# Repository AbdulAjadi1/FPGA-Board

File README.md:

# Custom Zynq FPGA Development Board

A custom-designed 8-layer FPGA development board based on the Xilinx Zynq-7000 SoC, featuring DDR3 memory, high-speed interfaces, and multi-rail power architecture. Designed from schematic through PCB layout and hardware bring-up.

---

<h2>🎥 FPGA Board Overview Demo</h2>

<h2>🔬 Full DDR3 Bring-Up Walkthrough (Vivado → Vitis)</h2>

<h2>💾 QSPI Flash Bring-Up Demo</h2>

<h2>🔌 UART Using EMIO and DDR3 test</h2>

---

**Custom Zynq-7000 FPGA Development Board**

**Overview**

This project is a custom FPGA development board inspired by the Digilent Arty Z7 platform, designed around the Xilinx Zynq-7000 SoC. The board serves as a general-purpose hardware development and learning platform, with an emphasis on FPGA and ARM (PS/PL) co-design, sound, power and signal-integrity practices, manufacturable industry-style PCB layout, and realistic interfaces commonly used in embedded and FPGA systems. The design is intended for advanced manufacturing and assembly at JLCPCB.

The project targets entry-level to junior FPGA and hardware engineering roles and focuses on demonstrating practical, board-level engineering decisions rather than a minimal breakout-style design.

**Project Status:**

## 🧪 Bring-Up & Validation

- ✅ DDR3 bring-up completed with successful memory test execution  
- ✅ QSPI flash configuration verified  
- ✅ FTDI USB-to-JTAG interface operational for programming and debug  
- ✅ Multi-rail power system validated 
- ✅ AXI GPIO controlling user LEDs and RGB LEDs confirmed  
- ✅ PS clocking and PLL configuration stable

**KEY FEATURES:**
- Xilinx Zynq-7000 SoC (Z7-20 / XC7Z020 class)
- DDR3 SDRAM (PS memory)
- HDMI interface (video output)
- Ethernet PHY (10/100/1000 Mbps)
- USB Host
- USB-JTAG interface
- SPDIF / TOSLINK interface
- QSPI Flash (boot storage)
- microSD card support
- PMOD / GPIO headers
- 40-pin Raspberry Pi interface
- On-board oscillators for PS and PL
- User LEDs, buttons, and switches
- Multi-rail power tree with switching regulators and LDOs

**DESIGN GOALS:**
- Follow Xilinx Zynq hardware design guidelines
- Implement correct decoupling, grounding, and plane usage
- Use controlled-impedance routing for high-speed interfaces
- Be compatible with low-cost PCB manufacturing and assembly
- Serve as a portfolio-quality hardware project

**HARDWARE ARCHITECTURE:**
- Zynq SoC
- ARM Cortex-A9 Processing System (PS)
- Programmable Logic (PL) fabric
- PS-to-PL interconnect exposed for custom designs
- Boot modes supported via QSPI / SD Memory
- DDR3 SDRAM connected to the PS:
- Length-matched address, control, and data groups
- Proper VREF routing and decoupling

**POWER TREE:**

**Input Sources:**

- 7-15V Barrel jack
- Raspberry pi 5V
- USB 5V

**Generated rails:**

- 1.0 V (FPGA core)

- 1.5 V (DDR3)

- 1.8 V (aux, IO)

- 3.3 V (IO and peripherals)

**PCB DESIGN DETAILS:**

- 8-layer PCB stackup

- Dedicated solid ground planeS

- Power planes for core rails

- Signal layers for controlled routing

- Thermal via stitching under FPGA ground regions

**Controlled impedance routing for:**

- DDR3 100Ω diff ±10%, 50Ω single ±10%

- HDMI 100Ω diff ±10%

- Ethernet  100Ω diff ±10%, 50Ω single ±10%

- USB 100Ω diff ±10%, 50Ω single ±10%

- SD  50Ω single ±10%

**INTENDED USE CASES:**

- FPGA and SoC learning platform

- PS/PL co-design experimentation

- HDL development and verification

- Embedded Linux bring-up (future work)

**TOOLS USED:**

- KiCad – schematic capture and PCB layout

- Xilinx Vivado – FPGA design and synthesis

- Vendor datasheets and Xilinx reference designs

- JLCPCB DFM/DFT tools

- JLCPCB Impedance calculator

**Author**

Designed and documented by Abdul Ajadi

Electronics / FPGA Hardware Engineer

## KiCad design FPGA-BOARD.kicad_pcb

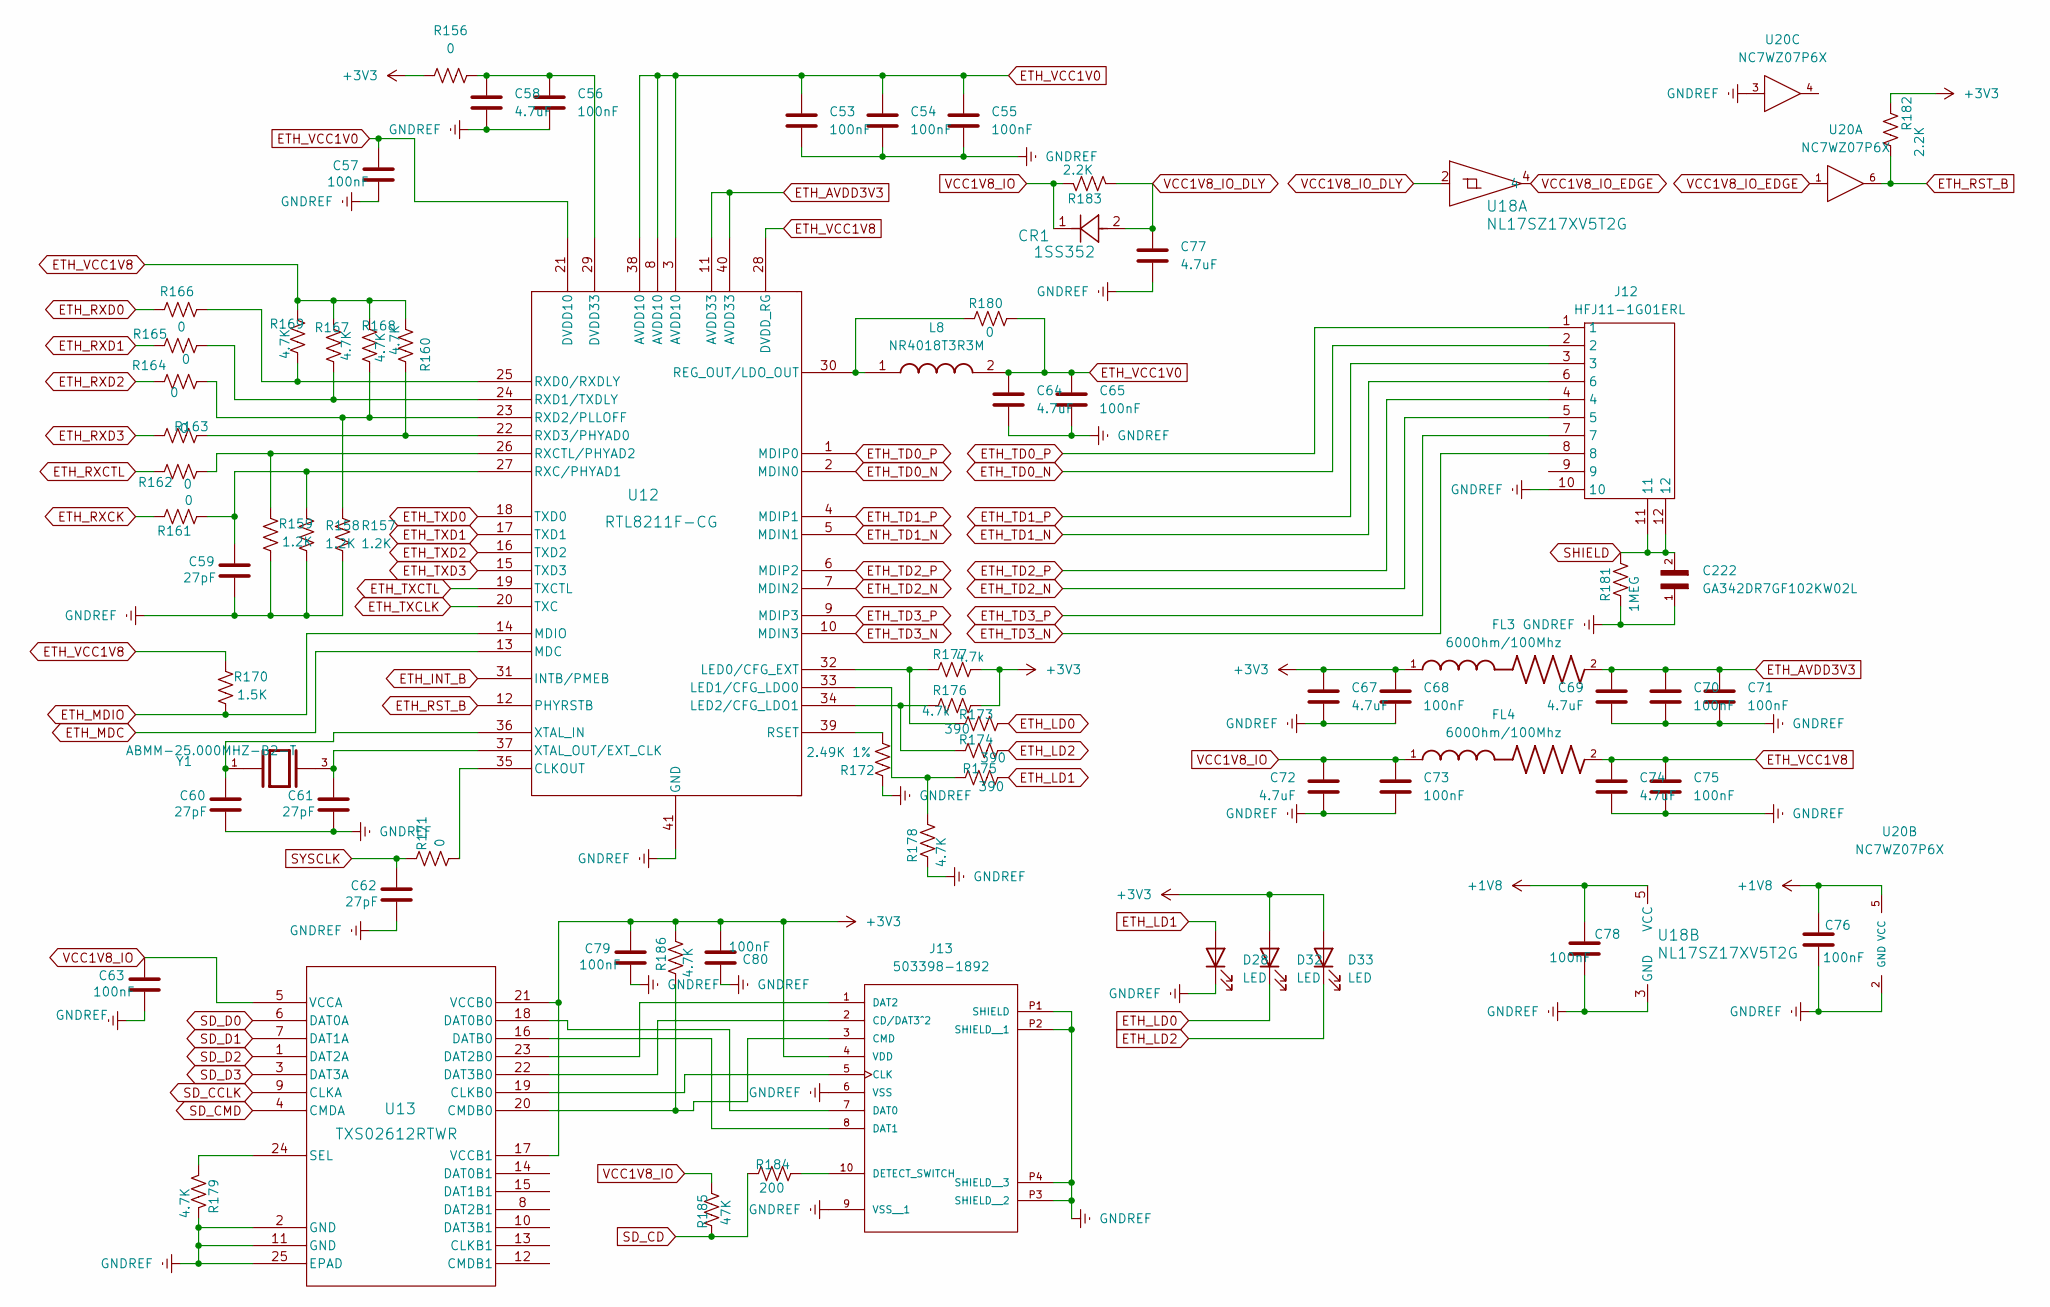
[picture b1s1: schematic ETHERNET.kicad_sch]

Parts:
C53, C54, C55, C56, C57, C63, C65, C68, C70, C71, C73, C75, C76, C78, C79, C80: 100nF; C_0201_0603Metric; LCSC PN c307380
C58, C64, C67, C69, C72, C74, C77: 4.7uF; C_0402; LCSC PN C2858031
C59, C60, C61, C62: 27pF; C_0201_0603Metric; LCSC PN C161381
C222: GA342DR7GF102KW02L; CAPC4520X220N; LCSC PN C237595
CR1: 1SS352; USC_TOS; LCSC PN C15885
D28, D32, D33: LED; LED_0402_1005Metric; LCSC PN C130723
FL3, FL4: 600Ohm/100Mhz; BEADC1608X95N; LCSC PN C19330
J12: HFJ11-1G01ERL; HALO_FASTJACK; Mouser Part Number 493-HFJ11-1G01ERL
J13: 503398-1892; MOLEX_503398-1892; PARTREV 0; LCSC PN C428492
L8: NR4018T3R3M; Mouser Part Number 963-NR4018T3R3M
R156, R171, R180: 0; R_0402; LCSC PN C106231
R157, R158, R159: 1.2K; R_0201_0603Metric; LCSC PN C327393
R160, R167, R168, R169, R178, R179, R186: 4.7K; R_0201_0603Metric; LCSC PN C138135
R161, R162, R163, R164, R165, R166: 0; R_0201_0603Metric; LCSC PN c106228
R170: 1.5K; R_0402; LCSC PN C114759
R172: 2.49K 1%; R_0402; LCSC PN C145071
R173, R174, R175: 390; R_0402; LCSC PN C137997
R176, R177: 4.7k; R_0402; LCSC PN C105871
R181: 1MEG; R_0402; LCSC PN C138033
R182, R183: 2.2K; R_0402; LCSC PN c114762
R184: 200; R_0402; LCSC PN C114764
R185: 47K; R_0402; LCSC PN C93943
U12: RTL8211F-CG; RTL8211F-CG_RTK; LCSC PN C187932
U13: TXS02612RTWR; RTW24_2P45X2P45; LCSC PN C140276
U18: NL17SZ17XV5T2G; SOT553-5_ONS; LCSC PN C152502
U20: NC7WZ07P6X; MPN NC7WZ07P6X; LCSC PN C95342
Y1: ABMM-25.000MHZ-B2-T; XTAL_ABMM-25.000MHZ-B2-T; PARTREV 02.26.12; LCSC PN C596927

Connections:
+1V8: C76.1, C78.1, U18.5 (VCC), U20.5 (VCC); also elsewhere on the board
+3V3: C67.1, C68.1, C79.1, C80.1, D32.2 (A), D33.2 (A), FL3.1, J13.4 (VDD), R156.2, R176.2, R177.2, R182.2, R186.2, U13.17 (VCCB1), U13.21 (VCCB0); also elsewhere on the board
ETH_AVDD3V3: C69.1, C70.1, C71.1, FL3.2, U12.11 (AVDD33), U12.40 (AVDD33)
ETH_INT_B: U12.31 (INTB/PMEB); also elsewhere on the board
ETH_LD0: D32.1 (K), R173.2
ETH_LD1: D28.2 (A), R175.2
ETH_LD2: D33.1 (K), R174.2
ETH_MDC: U12.13 (MDC); also elsewhere on the board
ETH_MDIO: R170.2, U12.14 (MDIO); also elsewhere on the board
ETH_RST_B: R182.1, U12.12 (PHYRSTB), U20.6; also elsewhere on the board
ETH_RXCK: R161.2; also elsewhere on the board
ETH_RXCTL: R162.2; also elsewhere on the board
ETH_RXD0: R166.2; also elsewhere on the board
ETH_RXD1: R165.2; also elsewhere on the board
ETH_RXD2: R164.2; also elsewhere on the board
ETH_RXD3: R163.2; also elsewhere on the board
ETH_TD0_N: J12.2, U12.2 (MDIN0)
ETH_TD0_P: J12.1, U12.1 (MDIP0)
ETH_TD1_N: J12.6, U12.5 (MDIN1)
ETH_TD1_P: J12.3, U12.4 (MDIP1)
ETH_TD2_N: J12.5, U12.7 (MDIN2)
ETH_TD2_P: J12.4, U12.6 (MDIP2)
ETH_TD3_N: J12.8, U12.10 (MDIN3)
ETH_TD3_P: J12.7, U12.9 (MDIP3)
ETH_TXCLK: U12.20 (TXC); also elsewhere on the board
ETH_TXCTL: U12.19 (TXCTL); also elsewhere on the board
ETH_TXD0: U12.18 (TXD0); also elsewhere on the board
ETH_TXD1: U12.17 (TXD1); also elsewhere on the board
ETH_TXD2: U12.16 (TXD2); also elsewhere on the board
ETH_TXD3: U12.15 (TXD3); also elsewhere on the board
ETH_VCC1V0: C53.1, C54.1, C55.1, C57.1, C64.1, C65.1, L8.2, R180.2, U12.3 (AVDD10), U12.8 (AVDD10), U12.21 (DVDD10), U12.38 (AVDD10)
ETH_VCC1V8: C74.1, C75.1, FL4.2, R160.1, R167.1, R168.1, R169.1, R170.1, U12.28 (DVDD_RG)
GNDREF: C53.2, C54.2, C55.2, C56.2, C57.2, C58.2, C59.2, C60.2, C61.2, C62.2, C63.2, C64.2, C65.2, C67.2, C68.2, C69.2, C70.2, C71.2, C72.2, C73.2, C74.2, C75.2, C76.2, C77.2, C78.2, C79.2, C80.2, C222.1, D28.1 (K), J12.10, J13.6 (VSS), J13.9 (VSS__1), J13.P1 (SHIELD), J13.P2 (SHIELD__1), J13.P3 (SHIELD__2), J13.P4 (SHIELD__3), R157.2, R158.2, R159.2, R172.1, R178.1, R179.1, R181.1, U12.41 (GND), U13.2 (GND), U13.11 (GND), U13.25 (EPAD), U13.V, U18.3 (GND), U20.2 (GND), U20.3; also elsewhere on the board
unnamed: J13.2 (CD/DAT3^2), U13.22 (DAT3B0)
unnamed: J13.5 (CLK), U13.19 (CLKB0)
unnamed: J13.3 (CMD), R186.1, U13.20 (CMDB0)
unnamed: J13.7 (DAT0), U13.18 (DAT0B0)
unnamed: J13.8 (DAT1), U13.16 (DATB0)
unnamed: J13.1 (DAT2), U13.23 (DAT2B0)
unnamed: J13.10 (DETECT_SWITCH), R184.2
unnamed: R171.2, U12.35 (CLKOUT)
unnamed: C56.1, C58.1, R156.1, U12.29 (DVDD33)
unnamed: R173.1, R177.1, U12.32 (LED0/CFG_EXT)
unnamed: R175.1, R178.2, U12.33 (LED1/CFG_LDO0)
unnamed: R174.1, R176.1, U12.34 (LED2/CFG_LDO1)
unnamed: L8.1, R180.1, U12.30 (REG_OUT/LDO_OUT)
unnamed: R172.2, U12.39 (RSET)
unnamed: R159.1, R162.1, U12.26 (RXCTL/PHYAD2)
unnamed: C59.1, R158.1, R161.1, U12.27 (RXC/PHYAD1)
unnamed: R166.1, R169.2, U12.25 (RXD0/RXDLY)
unnamed: R165.1, R167.2, U12.24 (RXD1/TXDLY)
unnamed: R157.1, R164.1, R168.2, U12.23 (RXD2/PLLOFF)
unnamed: R160.2, R163.1, U12.22 (RXD3/PHYAD0)
unnamed: C60.1, U12.36 (XTAL_IN), Y1.1
unnamed: C61.1, U12.37 (XTAL_OUT/EXT_CLK), Y1.3
unnamed: R179.2, U13.24 (SEL)
SD_CCLK: U13.9 (CLKA); also elsewhere on the board
SD_CD: R184.1, R185.1; also elsewhere on the board
SD_CMD: U13.4 (CMDA); also elsewhere on the board
SD_D0: U13.6 (DAT0A); also elsewhere on the board
SD_D1: U13.7 (DAT1A); also elsewhere on the board
SD_D2: U13.1 (DAT2A); also elsewhere on the board
SD_D3: U13.3 (DAT3A); also elsewhere on the board
SHIELD: C222.2, J12.11, J12.12, R181.2
SYSCLK: C62.1, R171.1; also elsewhere on the board
VCC1V8_IO: C63.1, C72.1, C73.1, CR1.1, FL4.1, R183.1, R185.2, U13.5 (VCCA); also elsewhere on the board
VCC1V8_IO_DLY: C77.1, CR1.2, R183.2, U18.2
VCC1V8_IO_EDGE: U18.4, U20.1

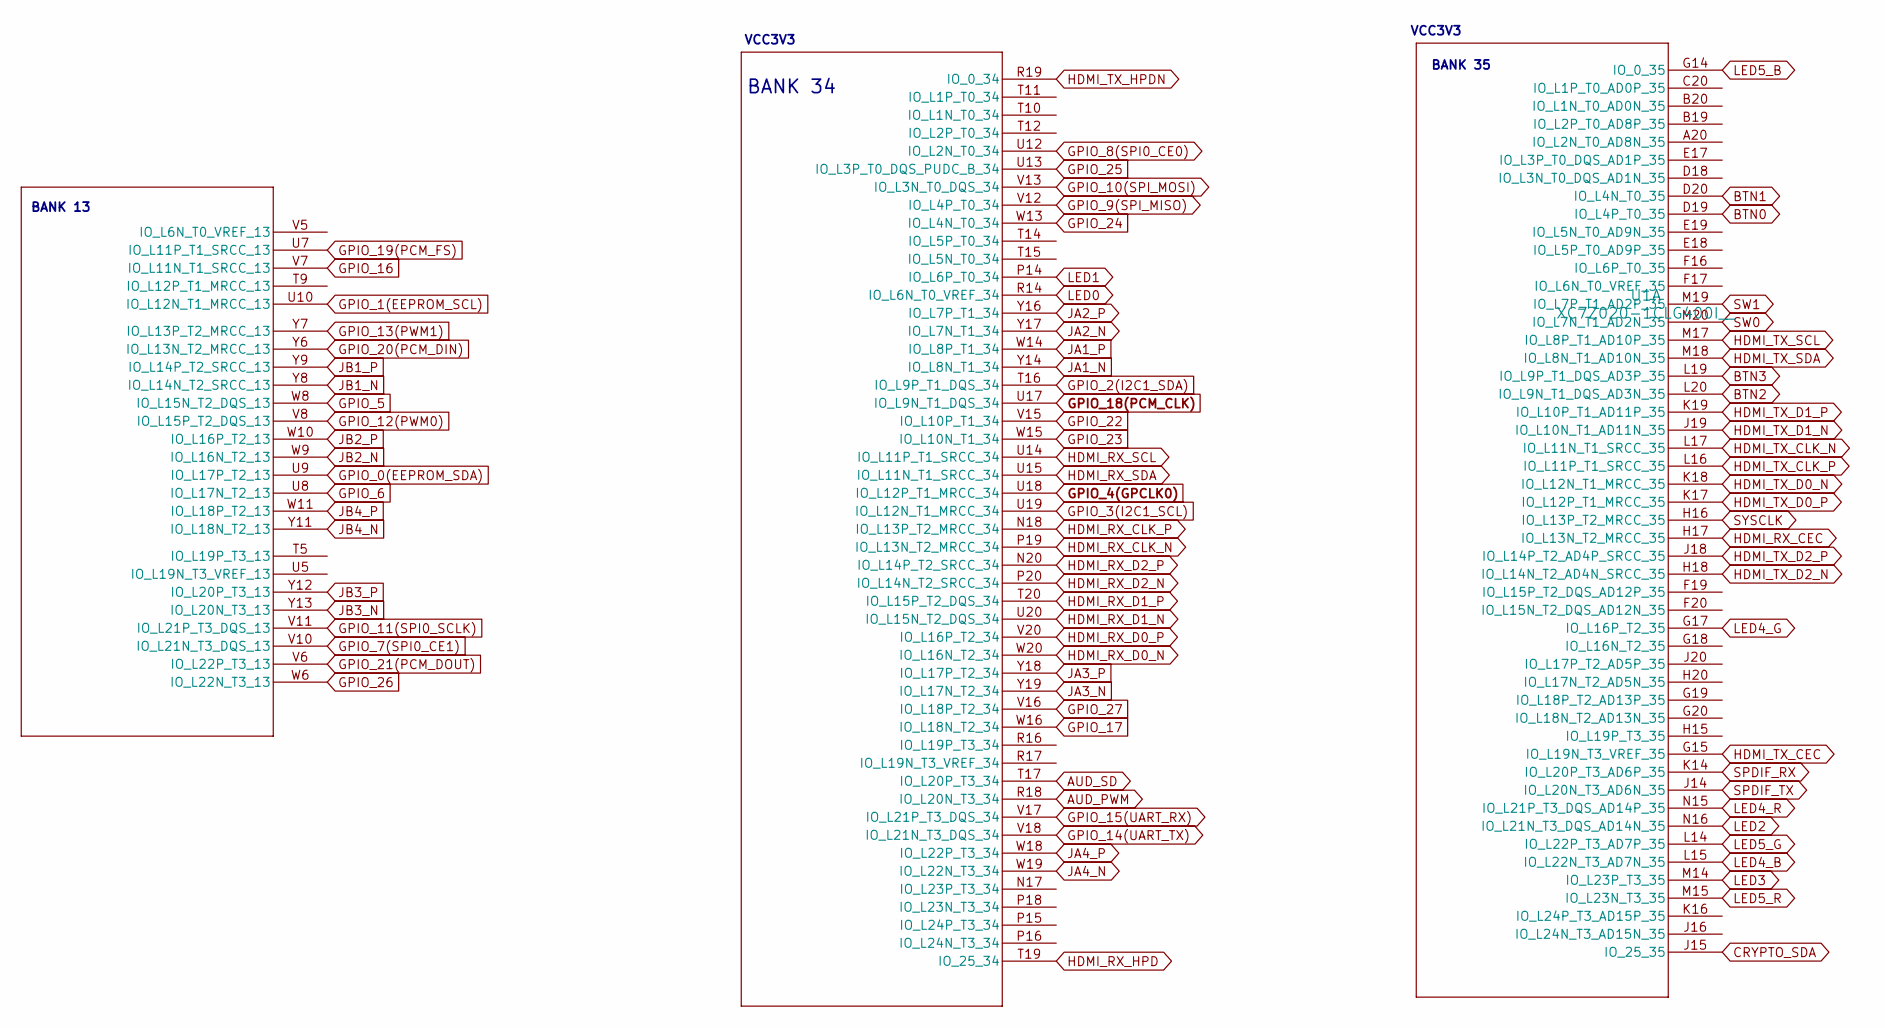
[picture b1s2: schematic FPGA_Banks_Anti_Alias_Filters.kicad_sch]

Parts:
U1: XC7Z020-1CLG400I__; CLG400_ZYNQ-7000_AMD; LCSC PN C1519081

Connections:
AUD_PWM: U1.R18 (IO_L20N_T3_34); also elsewhere on the board
AUD_SD: U1.T17 (IO_L20P_T3_34); also elsewhere on the board
BTN0: U1.D19 (IO_L4P_T0_35); also elsewhere on the board
BTN1: U1.D20 (IO_L4N_T0_35); also elsewhere on the board
BTN2: U1.L20 (IO_L9N_T1_DQS_AD3N_35); also elsewhere on the board
BTN3: U1.L19 (IO_L9P_T1_DQS_AD3P_35); also elsewhere on the board
CRYPTO_SDA: U1.J15 (IO_25_35); also elsewhere on the board
GPIO_0(EEPROM_SDA): U1.U9 (IO_L17P_T2_13); also elsewhere on the board
GPIO_1(EEPROM_SCL): U1.U10 (IO_L12N_T1_MRCC_13); also elsewhere on the board
GPIO_2(I2C1_SDA): U1.T16 (IO_L9P_T1_DQS_34); also elsewhere on the board
GPIO_3(I2C1_SCL): U1.U19 (IO_L12N_T1_MRCC_34); also elsewhere on the board
GPIO_4(GPCLK0): U1.U18 (IO_L12P_T1_MRCC_34); also elsewhere on the board
GPIO_5: U1.W8 (IO_L15N_T2_DQS_13); also elsewhere on the board
GPIO_6: U1.U8 (IO_L17N_T2_13); also elsewhere on the board
GPIO_7(SPI0_CE1): U1.V10 (IO_L21N_T3_DQS_13); also elsewhere on the board
GPIO_8(SPI0_CE0): U1.U12 (IO_L2N_T0_34); also elsewhere on the board
GPIO_9(SPI_MISO): U1.V12 (IO_L4P_T0_34); also elsewhere on the board
GPIO_10(SPI_MOSI): U1.V13 (IO_L3N_T0_DQS_34); also elsewhere on the board
GPIO_11(SPI0_SCLK): U1.V11 (IO_L21P_T3_DQS_13); also elsewhere on the board
GPIO_12(PWM0): U1.V8 (IO_L15P_T2_DQS_13); also elsewhere on the board
GPIO_13(PWM1): U1.Y7 (IO_L13P_T2_MRCC_13); also elsewhere on the board
GPIO_14(UART_TX): U1.V18 (IO_L21N_T3_DQS_34); also elsewhere on the board
GPIO_15(UART_RX): U1.V17 (IO_L21P_T3_DQS_34); also elsewhere on the board
GPIO_16: U1.V7 (IO_L11N_T1_SRCC_13); also elsewhere on the board
GPIO_17: U1.W16 (IO_L18N_T2_34); also elsewhere on the board
GPIO_18(PCM_CLK): U1.U17 (IO_L9N_T1_DQS_34); also elsewhere on the board
GPIO_19(PCM_FS): U1.U7 (IO_L11P_T1_SRCC_13); also elsewhere on the board
GPIO_20(PCM_DIN): U1.Y6 (IO_L13N_T2_MRCC_13); also elsewhere on the board
GPIO_21(PCM_DOUT): U1.V6 (IO_L22P_T3_13); also elsewhere on the board
GPIO_22: U1.V15 (IO_L10P_T1_34); also elsewhere on the board
GPIO_23: U1.W15 (IO_L10N_T1_34); also elsewhere on the board
GPIO_24: U1.W13 (IO_L4N_T0_34); also elsewhere on the board
GPIO_25: U1.U13 (IO_L3P_T0_DQS_PUDC_B_34); also elsewhere on the board
GPIO_26: U1.W6 (IO_L22N_T3_13); also elsewhere on the board
GPIO_27: U1.V16 (IO_L18P_T2_34); also elsewhere on the board
HDMI_RX_CEC: U1.H17 (IO_L13N_T2_MRCC_35); also elsewhere on the board
HDMI_RX_CLK_N: U1.P19 (IO_L13N_T2_MRCC_34); also elsewhere on the board
HDMI_RX_CLK_P: U1.N18 (IO_L13P_T2_MRCC_34); also elsewhere on the board
HDMI_RX_D0_N: U1.W20 (IO_L16N_T2_34); also elsewhere on the board
HDMI_RX_D0_P: U1.V20 (IO_L16P_T2_34); also elsewhere on the board
HDMI_RX_D1_N: U1.U20 (IO_L15N_T2_DQS_34); also elsewhere on the board
HDMI_RX_D1_P: U1.T20 (IO_L15P_T2_DQS_34); also elsewhere on the board
HDMI_RX_D2_N: U1.P20 (IO_L14N_T2_SRCC_34); also elsewhere on the board
HDMI_RX_D2_P: U1.N20 (IO_L14P_T2_SRCC_34); also elsewhere on the board
HDMI_RX_HPD: U1.T19 (IO_25_34); also elsewhere on the board
HDMI_RX_SCL: U1.U14 (IO_L11P_T1_SRCC_34); also elsewhere on the board
HDMI_RX_SDA: U1.U15 (IO_L11N_T1_SRCC_34); also elsewhere on the board
HDMI_TX_CEC: U1.G15 (IO_L19N_T3_VREF_35); also elsewhere on the board
HDMI_TX_CLK_N: U1.L17 (IO_L11N_T1_SRCC_35); also elsewhere on the board
HDMI_TX_CLK_P: U1.L16 (IO_L11P_T1_SRCC_35); also elsewhere on the board
HDMI_TX_D0_N: U1.K18 (IO_L12N_T1_MRCC_35); also elsewhere on the board
HDMI_TX_D0_P: U1.K17 (IO_L12P_T1_MRCC_35); also elsewhere on the board
HDMI_TX_D1_N: U1.J19 (IO_L10N_T1_AD11N_35); also elsewhere on the board
HDMI_TX_D1_P: U1.K19 (IO_L10P_T1_AD11P_35); also elsewhere on the board
HDMI_TX_D2_N: U1.H18 (IO_L14N_T2_AD4N_SRCC_35); also elsewhere on the board
HDMI_TX_D2_P: U1.J18 (IO_L14P_T2_AD4P_SRCC_35); also elsewhere on the board
HDMI_TX_HPDN: U1.R19 (IO_0_34); also elsewhere on the board
HDMI_TX_SCL: U1.M17 (IO_L8P_T1_AD10P_35); also elsewhere on the board
HDMI_TX_SDA: U1.M18 (IO_L8N_T1_AD10N_35); also elsewhere on the board
JA1_N: U1.Y14 (IO_L8N_T1_34); also elsewhere on the board
JA1_P: U1.W14 (IO_L8P_T1_34); also elsewhere on the board
JA2_N: U1.Y17 (IO_L7N_T1_34); also elsewhere on the board
JA2_P: U1.Y16 (IO_L7P_T1_34); also elsewhere on the board
JA3_N: U1.Y19 (IO_L17N_T2_34); also elsewhere on the board
JA3_P: U1.Y18 (IO_L17P_T2_34); also elsewhere on the board
JA4_N: U1.W19 (IO_L22N_T3_34); also elsewhere on the board
JA4_P: U1.W18 (IO_L22P_T3_34); also elsewhere on the board
JB1_N: U1.Y8 (IO_L14N_T2_SRCC_13); also elsewhere on the board
JB1_P: U1.Y9 (IO_L14P_T2_SRCC_13); also elsewhere on the board
JB2_N: U1.W9 (IO_L16N_T2_13); also elsewhere on the board
JB2_P: U1.W10 (IO_L16P_T2_13); also elsewhere on the board
JB3_N: U1.Y13 (IO_L20N_T3_13); also elsewhere on the board
JB3_P: U1.Y12 (IO_L20P_T3_13); also elsewhere on the board
JB4_N: U1.Y11 (IO_L18N_T2_13); also elsewhere on the board
JB4_P: U1.W11 (IO_L18P_T2_13); also elsewhere on the board
LED0: U1.R14 (IO_L6N_T0_VREF_34); also elsewhere on the board
LED1: U1.P14 (IO_L6P_T0_34); also elsewhere on the board
LED2: U1.N16 (IO_L21N_T3_DQS_AD14N_35); also elsewhere on the board
LED3: U1.M14 (IO_L23P_T3_35); also elsewhere on the board
LED4_B: U1.L15 (IO_L22N_T3_AD7N_35); also elsewhere on the board
LED4_G: U1.G17 (IO_L16P_T2_35); also elsewhere on the board
LED4_R: U1.N15 (IO_L21P_T3_DQS_AD14P_35); also elsewhere on the board
LED5_B: U1.G14 (IO_0_35); also elsewhere on the board
LED5_G: U1.L14 (IO_L22P_T3_AD7P_35); also elsewhere on the board
LED5_R: U1.M15 (IO_L23N_T3_35); also elsewhere on the board
SPDIF_RX: U1.K14 (IO_L20P_T3_AD6P_35); also elsewhere on the board
SPDIF_TX: U1.J14 (IO_L20N_T3_AD6N_35); also elsewhere on the board
SW0: U1.M20 (IO_L7N_T1_AD2N_35); also elsewhere on the board
SW1: U1.M19 (IO_L7P_T1_AD2P_35); also elsewhere on the board
SYSCLK: U1.H16 (IO_L13P_T2_MRCC_35); also elsewhere on the board

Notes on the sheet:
BANK 35
BANK 34
VCC3V3
BANK 13

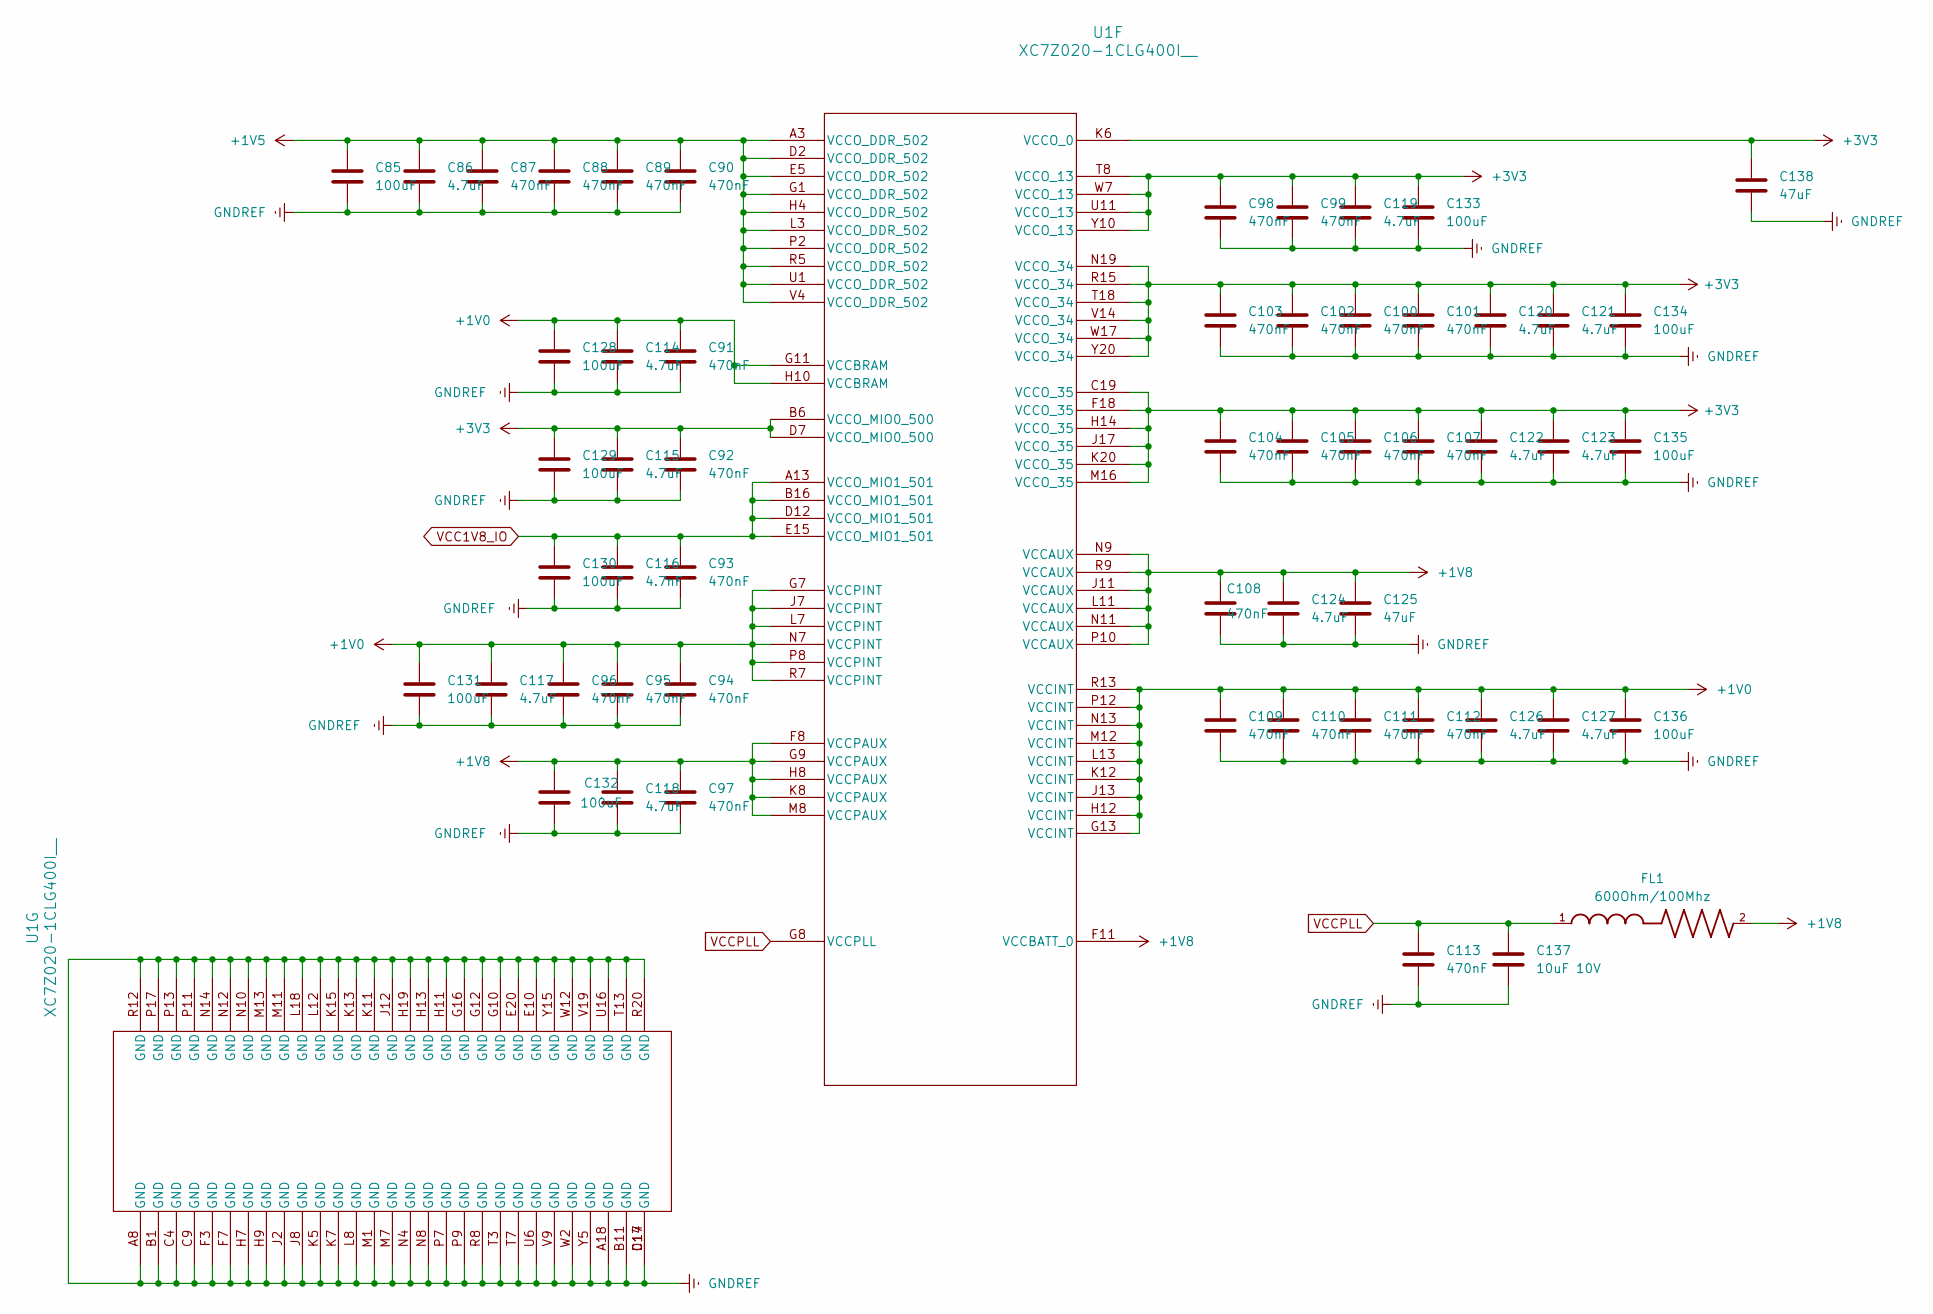
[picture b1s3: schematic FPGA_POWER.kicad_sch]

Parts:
C85, C128, C129, C130, C131, C132, C133, C134, C135, C136: 100uF; C_0805; LCSC PN c141660
C86, C114, C115, C117, C118, C119, C120, C121, C122, C123, C124, C126, C127: 4.7uF; C_0402; LCSC PN C2858031
C87, C88, C89, C90, C91, C92, C93, C94, C95, C96, C97, C98, C99, C100, C101, C102, C103, C104, C105, C106, C107, C108, C109, C110, C111, C112, C113: 470nF; C_0201_0603Metric; LCSC PN C5383023
C116: 4.7nF; C_0402; LCSC PN c84705
C125, C138: 47uF; C_0805; LCSC PN C124129
C137: 10uF 10V; C_0805; LCSC PN C15850
FL1: 600Ohm/100Mhz; BEADC1608X95N; LCSC PN C19330
U1: XC7Z020-1CLG400I__; CLG400_ZYNQ-7000_AMD; LCSC PN C1519081

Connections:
+1V0: C91.1, C94.1, C95.1, C96.1, C109.1, C110.1, C111.1, C112.1, C114.1, C117.1, C126.1, C127.1, C128.1, C131.1, C136.1, U1.G7 (VCCPINT), U1.G11 (VCCBRAM), U1.G13 (VCCINT), U1.H10 (VCCBRAM), U1.H12 (VCCINT), U1.J7 (VCCPINT), U1.J13 (VCCINT), U1.K12 (VCCINT), U1.L7 (VCCPINT), U1.L13 (VCCINT), U1.M12 (VCCINT), U1.N7 (VCCPINT), U1.N13 (VCCINT), U1.P8 (VCCPINT), U1.P12 (VCCINT), U1.R7 (VCCPINT), U1.R13 (VCCINT); also elsewhere on the board
+1V5: C85.1, C86.1, C87.1, C88.1, C89.1, C90.1, U1.A3 (VCCO_DDR_502), U1.D2 (VCCO_DDR_502), U1.E5 (VCCO_DDR_502), U1.G1 (VCCO_DDR_502), U1.H4 (VCCO_DDR_502), U1.L3 (VCCO_DDR_502), U1.P2 (VCCO_DDR_502), U1.R5 (VCCO_DDR_502), U1.U1 (VCCO_DDR_502), U1.V4 (VCCO_DDR_502); also elsewhere on the board
+1V8: C97.1, C108.1, C118.1, C124.1, C125.1, C132.1, FL1.2, U1.F8 (VCCPAUX), U1.F11 (VCCBATT_0), U1.G9 (VCCPAUX), U1.H8 (VCCPAUX), U1.J11 (VCCAUX), U1.K8 (VCCPAUX), U1.L11 (VCCAUX), U1.M8 (VCCPAUX), U1.N9 (VCCAUX), U1.N11 (VCCAUX), U1.P10 (VCCAUX), U1.R9 (VCCAUX); also elsewhere on the board
+3V3: C92.1, C98.1, C99.1, C100.1, C101.1, C102.1, C103.1, C104.1, C105.1, C106.1, C107.1, C115.1, C119.1, C120.1, C121.1, C122.1, C123.1, C129.1, C133.1, C134.1, C135.1, C138.1, U1.B6 (VCCO_MIO0_500), U1.C19 (VCCO_35), U1.D7 (VCCO_MIO0_500), U1.F18 (VCCO_35), U1.H14 (VCCO_35), U1.J17 (VCCO_35), U1.K6 (VCCO_0), U1.K20 (VCCO_35), U1.M16 (VCCO_35), U1.N19 (VCCO_34), U1.R15 (VCCO_34), U1.T8 (VCCO_13), U1.T18 (VCCO_34), U1.U11 (VCCO_13), U1.V14 (VCCO_34), U1.W7 (VCCO_13), U1.W17 (VCCO_34), U1.Y10 (VCCO_13), U1.Y20 (VCCO_34); also elsewhere on the board
GNDREF: C85.2, C86.2, C87.2, C88.2, C89.2, C90.2, C91.2, C92.2, C93.2, C94.2, C95.2, C96.2, C97.2, C98.2, C99.2, C100.2, C101.2, C102.2, C103.2, C104.2, C105.2, C106.2, C107.2, C108.2, C109.2, C110.2, C111.2, C112.2, C113.2, C114.2, C115.2, C116.2, C117.2, C118.2, C119.2, C120.2, C121.2, C122.2, C123.2, C124.2, C125.2, C126.2, C127.2, C128.2, C129.2, C130.2, C131.2, C132.2, C133.2, C134.2, C135.2, C136.2, C137.2, C138.2, U1.A8 (GND), U1.A18 (GND), U1.B1 (GND), U1.B11 (GND), U1.C4 (GND), U1.C9 (GND), U1.C14 (GND), U1.D17 (GND), U1.E10 (GND), U1.E20 (GND), U1.F3 (GND), U1.F7 (GND), U1.G10 (GND), U1.G12 (GND), U1.G16 (GND), U1.H7 (GND), U1.H9 (GND), U1.H11 (GND), U1.H13 (GND), U1.H19 (GND), U1.J2 (GND), U1.J8 (GND), U1.J12 (GND), U1.K5 (GND), U1.K7 (GND), U1.K11 (GND), U1.K13 (GND), U1.K15 (GND), U1.L8 (GND), U1.L12 (GND), U1.L18 (GND), U1.M1 (GND), U1.M7 (GND), U1.M11 (GND), U1.M13 (GND), U1.N4 (GND), U1.N8 (GND), U1.N10 (GND), U1.N12 (GND), U1.N14 (GND), U1.P7 (GND), U1.P9 (GND), U1.P11 (GND), U1.P13 (GND), U1.P17 (GND), U1.R8 (GND), U1.R12 (GND), U1.R20 (GND), U1.T3 (GND), U1.T7 (GND), U1.T13 (GND), U1.U6 (GND), U1.U16 (GND), U1.V9 (GND), U1.V19 (GND), U1.W2 (GND), U1.W12 (GND), U1.Y5 (GND), U1.Y15 (GND); also elsewhere on the board
VCC1V8_IO: C93.1, C116.1, C130.1, U1.A13 (VCCO_MIO1_501), U1.B16 (VCCO_MIO1_501), U1.D12 (VCCO_MIO1_501), U1.E15 (VCCO_MIO1_501); also elsewhere on the board
VCCPLL: C113.1, C137.1, FL1.1, U1.G8 (VCCPLL)

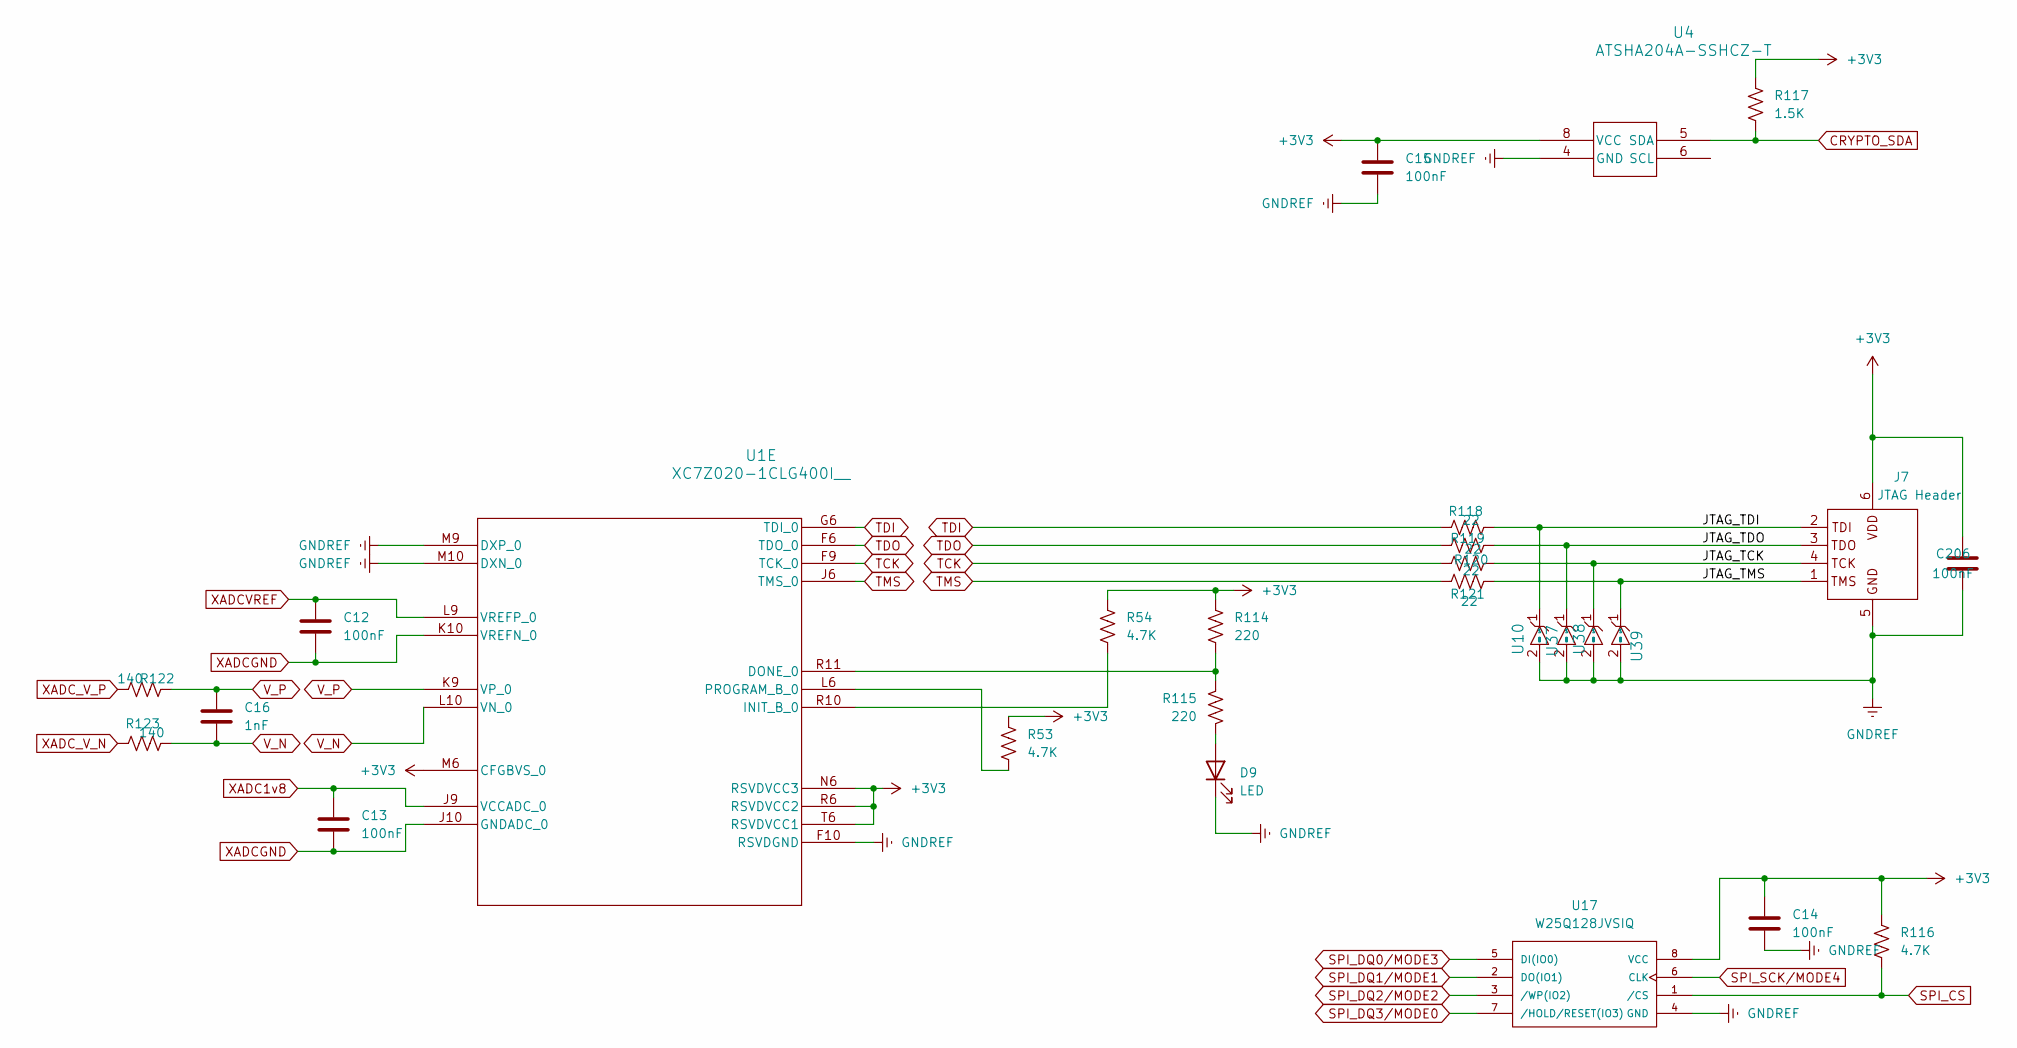
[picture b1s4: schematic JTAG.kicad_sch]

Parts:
C12, C13, C14, C15, C206: 100nF; C_0201_0603Metric; LCSC PN c307380
C16: 1nF; C_0402; LCSC PN C77018
D9: LED; LED_0402_1005Metric; LCSC PN C130723
J7: JTAG Header; PinHeader_1x06_P2.54mm_Vertical
R53, R54, R116: 4.7K; R_0201_0603Metric; LCSC PN C138135
R114, R115: 220; R_0402; LCSC PN C112291
R117: 1.5K; R_0402; LCSC PN C114759
R118, R119, R120, R121: 22; R_0201_0603Metric; LCSC PN C270355
R122, R123: 140; R_0402; LCSC PN C327016
U1: XC7Z020-1CLG400I__; CLG400_ZYNQ-7000_AMD; LCSC PN C1519081
U4: ATSHA204A-SSHCZ-T; SOIC8_4P9X3P9MC_MCH; LCSC PN C616025
U10, U37, U38, U39: TPD1E05U06DPYR; DIO_TPD1E05U06DPYR; LCSC PN C436349
U17: W25Q128JVSIQ; SOIC127P790X216-8N; PARTREV I; LCSC PN C97521

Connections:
+3V3: C14.1, C15.1, C206.1, J7.6 (VDD), R53.1, R54.1, R114.1, R116.1, R117.1, U1.M6 (CFGBVS_0), U1.N6 (RSVDVCC3), U1.R6 (RSVDVCC2), U1.T6 (RSVDVCC1), U4.8 (VCC), U17.8 (VCC); also elsewhere on the board
/JTAG/JTAG_TCK: J7.4 (TCK), R120.2, U38.1 (I/O)
/JTAG/JTAG_TDI: J7.2 (TDI), R118.2, U10.1 (I/O)
/JTAG/JTAG_TDO: J7.3 (TDO), R119.2, U37.1 (I/O)
/JTAG/JTAG_TMS: J7.1 (TMS), R121.2, U39.1 (I/O)
CRYPTO_SDA: R117.2, U4.5 (SDA); also elsewhere on the board
GNDREF: C14.2, C15.2, C206.2, D9.1 (K), J7.5 (GND), U1.F10 (RSVDGND), U1.M9 (DXP_0), U1.M10 (DXN_0), U4.4 (GND), U10.2 (GND), U17.4 (GND), U37.2 (GND), U38.2 (GND), U39.2 (GND); also elsewhere on the board
unnamed: D9.2 (A), R115.2
unnamed: R114.2, R115.1, U1.R11 (DONE_0)
unnamed: R54.2, U1.R10 (INIT_B_0)
unnamed: R53.2, U1.L6 (PROGRAM_B_0)
SPI_CS: R116.2, U17.1 (/CS); also elsewhere on the board
SPI_DQ0/MODE3: U17.5 (DI(IO0)); also elsewhere on the board
SPI_DQ1/MODE1: U17.2 (DO(IO1)); also elsewhere on the board
SPI_DQ2/MODE2: U17.3 (/WP(IO2)); also elsewhere on the board
SPI_DQ3/MODE0: U17.7 (/HOLD/RESET(IO3)); also elsewhere on the board
SPI_SCK/MODE4: U17.6 (CLK); also elsewhere on the board
TCK: R120.1, U1.F9 (TCK_0); also elsewhere on the board
TDI: R118.1, U1.G6 (TDI_0); also elsewhere on the board
TDO: R119.1, U1.F6 (TDO_0); also elsewhere on the board
TMS: R121.1, U1.J6 (TMS_0); also elsewhere on the board
V_N: C16.2, R123.2, U1.L10 (VN_0)
V_P: C16.1, R122.2, U1.K9 (VP_0)
XADC1v8: C13.1, U1.J9 (VCCADC_0)
XADCGND: C12.2, C13.2, U1.J10 (GNDADC_0), U1.K10 (VREFN_0); also elsewhere on the board
XADCVREF: C12.1, U1.L9 (VREFP_0); also elsewhere on the board
XADC_V_N: R123.1; also elsewhere on the board
XADC_V_P: R122.1; also elsewhere on the board
